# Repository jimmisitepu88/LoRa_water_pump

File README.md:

# LoRa_water_pump
Control Water Pump with LoRa

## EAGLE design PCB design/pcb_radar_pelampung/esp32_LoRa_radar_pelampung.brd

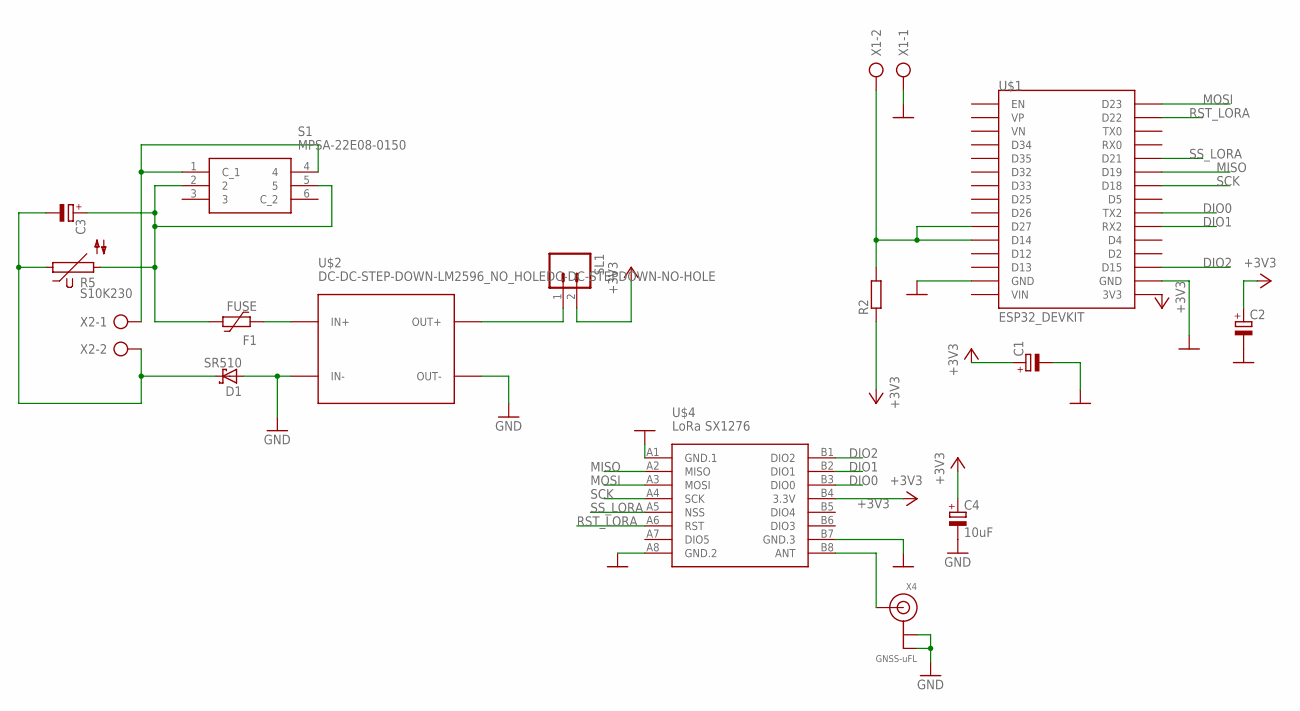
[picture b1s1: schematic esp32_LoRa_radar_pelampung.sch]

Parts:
C1, C2: CPOL-EUE5-8.5; E5-8,5
C3: CPOL-EUE5-13; E5-13
C4: 10uF; E2,5-6
D1: SR510; SMB
F1: FUSE; 1812L
R2: R-EU_0309/12; 0309/12
R5: S10K230
S1: MPSA-22E08-0150; MPSA22E080150
SL1: M02; 02P
U$1: ESP32_DEVKIT
U$2: DC-DC-STEP-DOWN-LM2596_NO_HOLEDC-DC-STEPDOWN-NO-H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; DC-DC-STEP-DOWN-LM2596_NO_HOLE
U$4: LoRa SX1276; WIRELESS-LORA-RFM95W#SMD
X1, X2: AK300/2
X4: GNSS-uFL; U.FL

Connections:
+3V3: C1.+, C2.+, C4.+, R2.1, SL1.2, U$1.3V3, U$4.B4 (3.3V)
DIO0: U$1.TX2, U$4.B3 (DIO0)
DIO1: U$1.RX2, U$4.B2 (DIO1)
DIO2: U$1.D15, U$4.B1 (DIO2)
GND: C1.-, C2.-, C4.-, D1.A, U$1.GND@1 (GND), U$1.GND@2 (GND), U$2.IN-, U$2.OUT-, U$4.A1 (GND.1), U$4.A8 (GND.2), U$4.B7 (GND.3), X1.1, X4.1 (GND), X4.2 (GND)
MISO: U$1.D19, U$4.A2 (MISO)
MOSI: U$1.D23, U$4.A3 (MOSI)
unnamed: F1.2, U$2.IN+
unnamed: SL1.1, U$2.OUT+
unnamed: R2.2, U$1.D14, U$1.D27, X1.2
unnamed: C3.-, D1.C, R5.1, X2.2
unnamed: S1.1 (C_1), S1.4, X2.1
unnamed: C3.+, F1.1, R5.2, S1.2, S1.5
unnamed: U$4.B8 (ANT), X4.3 (SIGNAL)
RST_LORA: U$1.D22, U$4.A6 (RST)
SCK: U$1.D18, U$4.A4 (SCK)
SS_LORA: U$1.D21, U$4.A5 (NSS)

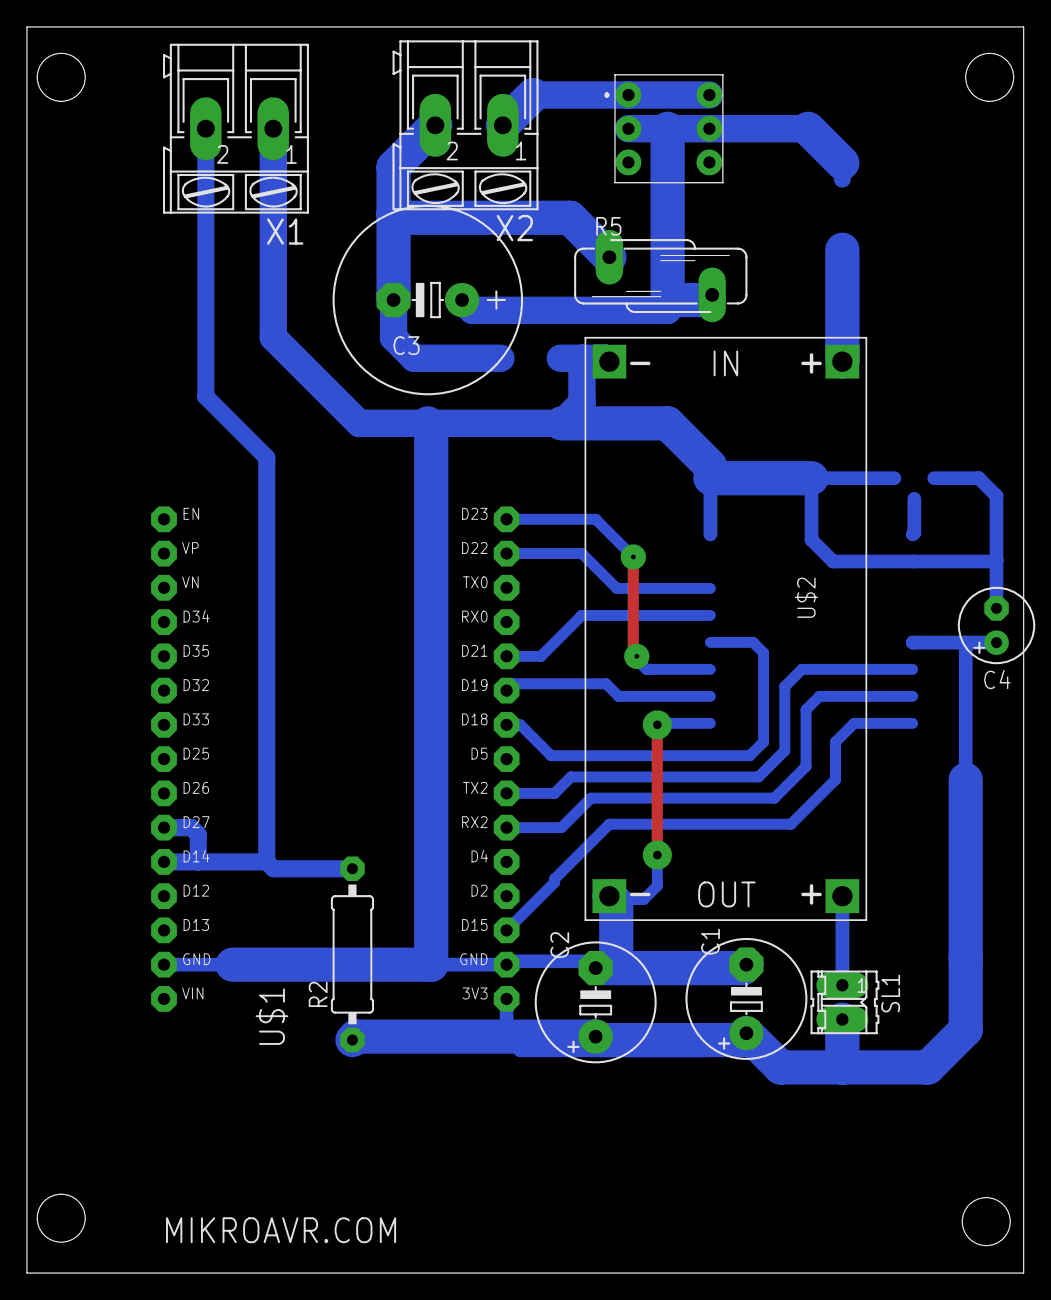
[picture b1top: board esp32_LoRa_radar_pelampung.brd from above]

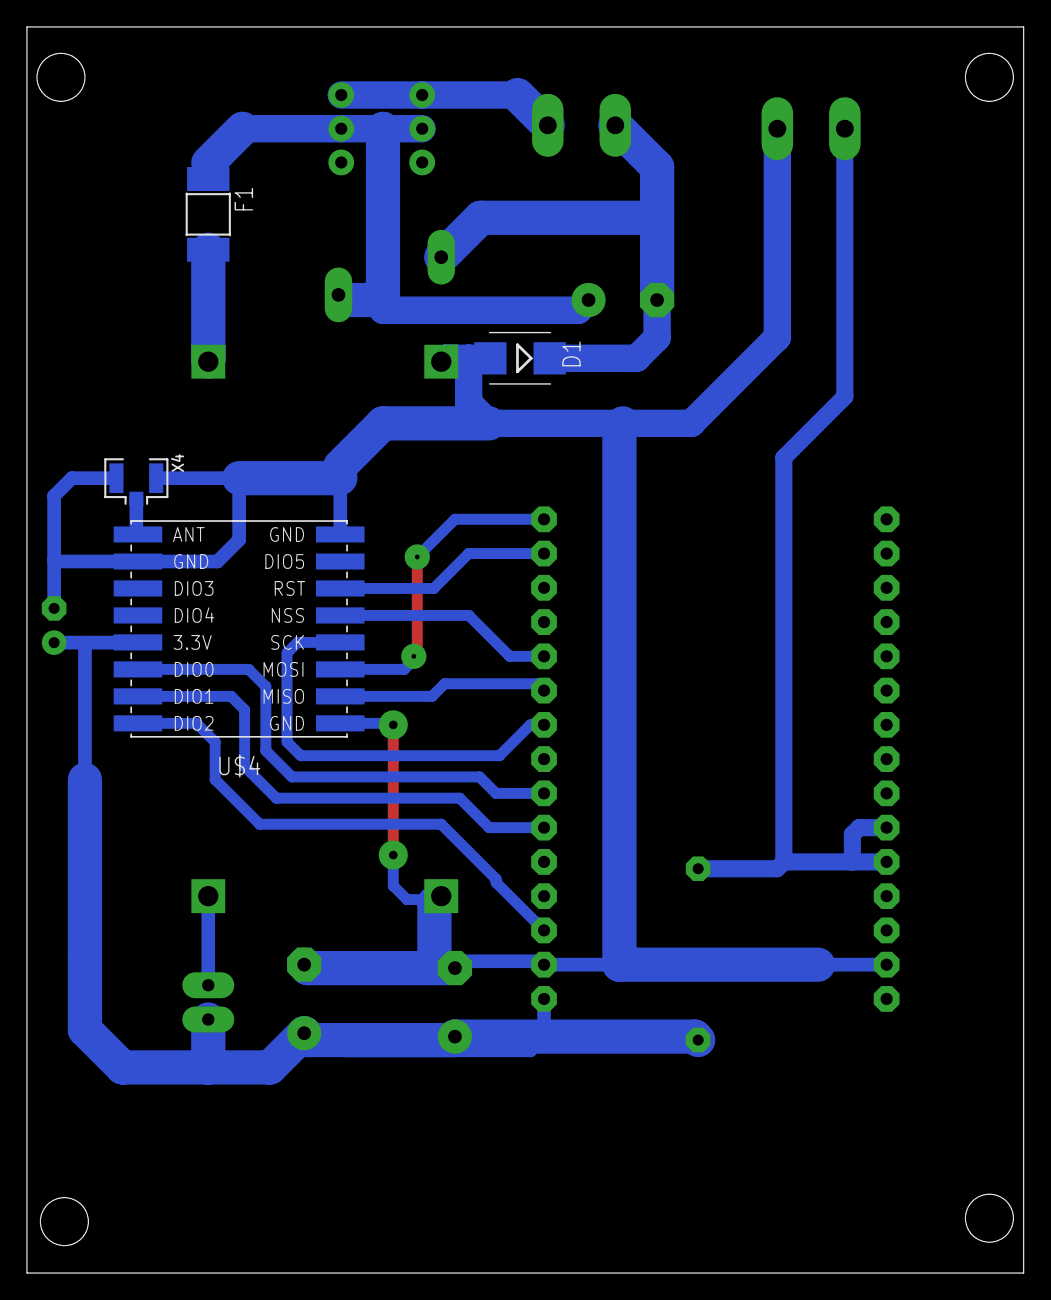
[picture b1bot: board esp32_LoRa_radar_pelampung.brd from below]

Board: 2 copper layers, 73.9 x 92.4 mm, 16 parts (4 on the bottom side), 17 nets.

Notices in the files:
parts and their libraries:
diy-modules: Released under the Creative Commons Attribution 4.0 International License: http://creativecommons.org/licenses/by/4.0
